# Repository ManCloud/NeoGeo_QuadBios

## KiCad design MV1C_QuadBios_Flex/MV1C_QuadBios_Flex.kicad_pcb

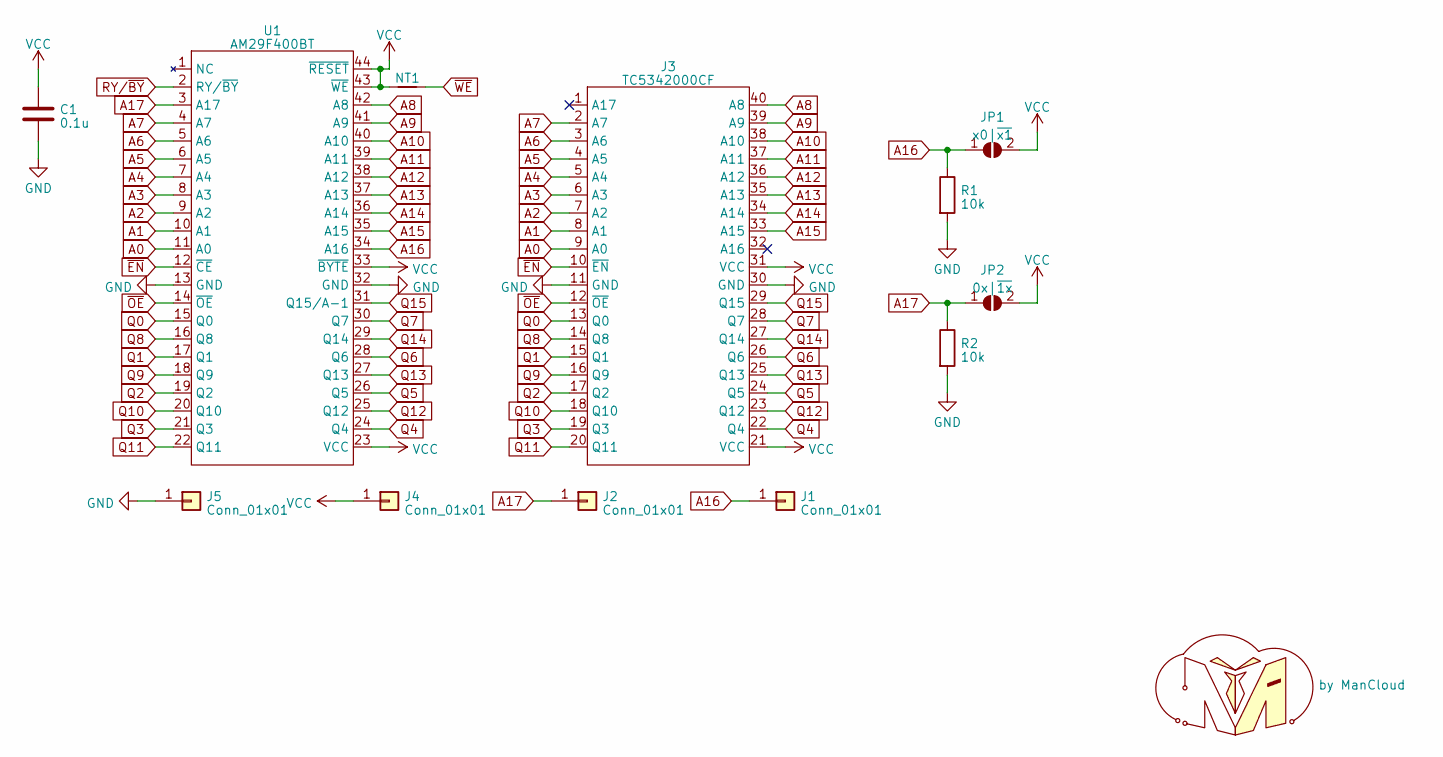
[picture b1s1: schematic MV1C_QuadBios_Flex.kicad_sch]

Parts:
C1: 0.1u; C_0603_1608Metric_Pad1.08x0.95mm_HandSolder
J1, J2, J4, J5: Conn_01x01; TestPoint_Keystone_5015_Micro-Minature
J3: TC5342000CF; TSOP-40_26.0x10.0mm_P1.27mm_JIG
JP1: x0|~{x1}; SolderJumper-2_P1.3mm_Open_TrianglePad1.0x1.5mm
JP2: 0x|~{1x}; SolderJumper-2_P1.3mm_Open_TrianglePad1.0x1.5mm
NT1: NetTie_2
R1, R2: 10k; R_0805_2012Metric_Pad1.20x1.40mm_HandSolder
U1: AM29F400BT; SO-44_P1.27
U2: by ManCloud; ManCloud_v2b_22mm

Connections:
A0: J3.9 (A0), U1.11 (A0)
A1: J3.8 (A1), U1.10 (A1)
A2: J3.7 (A2), U1.9 (A2)
A3: J3.6 (A3), U1.8 (A3)
A4: J3.5 (A4), U1.7 (A4)
A5: J3.4 (A5), U1.6 (A5)
A6: J3.3 (A6), U1.5 (A6)
A7: J3.2 (A7), U1.4 (A7)
A8: J3.40 (A8), U1.42 (A8)
A9: J3.39 (A9), U1.41 (A9)
A10: J3.38 (A10), U1.40 (A10)
A11: J3.37 (A11), U1.39 (A11)
A12: J3.36 (A12), U1.38 (A12)
A13: J3.35 (A13), U1.37 (A13)
A14: J3.34 (A14), U1.36 (A14)
A15: J3.33 (A15), U1.35 (A15)
A16: J1.1, JP1.1 (A), R1.1, U1.34 (A16)
A17: J2.1, JP2.1 (A), R2.1, U1.3 (A17)
GND: C1.2, J3.11 (GND), J3.30 (GND), J5.1, R1.2, R2.2, U1.13 (GND), U1.32 (GND)
Q0: J3.13 (Q0), U1.15 (Q0)
Q1: J3.15 (Q1), U1.17 (Q1)
Q2: J3.17 (Q2), U1.19 (Q2)
Q3: J3.19 (Q3), U1.21 (Q3)
Q4: J3.22 (Q4), U1.24 (Q4)
Q5: J3.24 (Q5), U1.26 (Q5)
Q6: J3.26 (Q6), U1.28 (Q6)
Q7: J3.28 (Q7), U1.30 (Q7)
Q8: J3.14 (Q8), U1.16 (Q8)
Q9: J3.16 (Q9), U1.18 (Q9)
Q10: J3.18 (Q10), U1.20 (Q10)
Q11: J3.20 (Q11), U1.22 (Q11)
Q12: J3.23 (Q12), U1.25 (Q12)
Q13: J3.25 (Q13), U1.27 (Q13)
Q14: J3.27 (Q14), U1.29 (Q14)
Q15: J3.29 (Q15), U1.31 (Q15/A-1)
RY/~BY: U1.2 (RY/~BY)
VCC: C1.1, J3.21 (VCC), J3.31 (VCC), J4.1, JP1.2 (B), JP2.2 (B), NT1.1, U1.23 (VCC), U1.33 (~BYTE), U1.43 (~WE), U1.44 (~RESET)
~EN: J3.10 (~EN), U1.12 (~CE)
~OE: J3.12 (~OE), U1.14 (~OE)

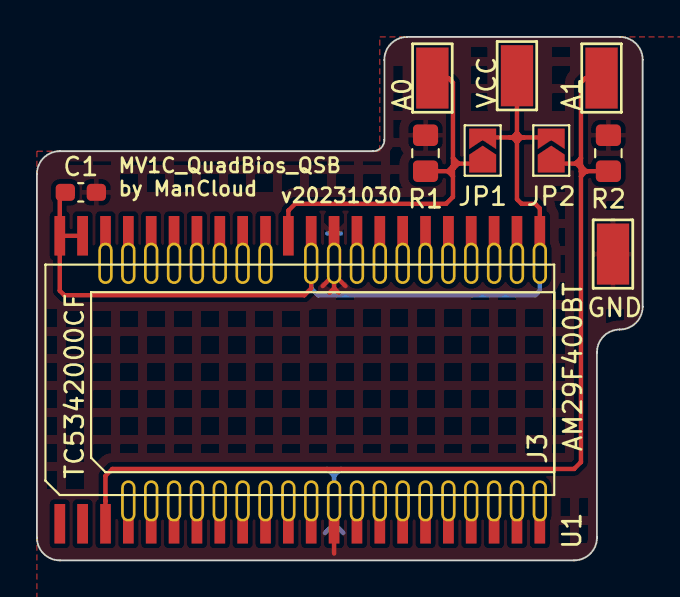
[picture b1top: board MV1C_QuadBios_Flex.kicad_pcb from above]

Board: 2 copper layers, 33.7 x 29.1 mm, 12 parts (1 on the bottom side), 38 nets.

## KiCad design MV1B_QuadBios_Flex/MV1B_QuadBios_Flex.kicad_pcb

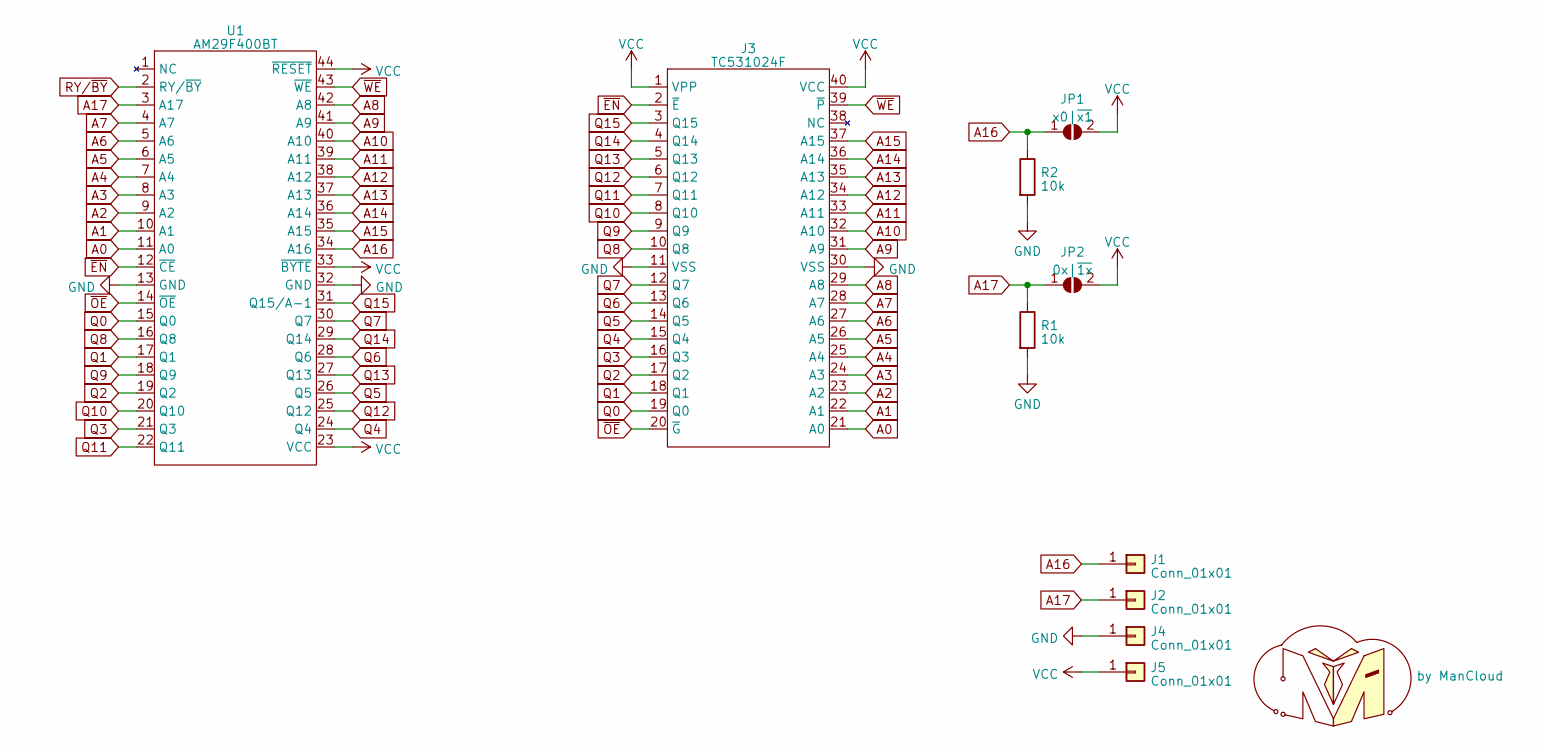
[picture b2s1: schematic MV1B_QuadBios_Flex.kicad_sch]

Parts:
J1, J2, J4, J5: Conn_01x01; TestPoint_Keystone_5015_Micro-Minature
J3: TC531024F; TSOP-40_26.0x10.0mm_P1.27mm_JIG
JP1: x0|~{x1}; SolderJumper-2_P1.3mm_Open_TrianglePad1.0x1.5mm
JP2: 0x|~{1x}; SolderJumper-2_P1.3mm_Open_TrianglePad1.0x1.5mm
R1, R2: 10k; R_0805_2012Metric_Pad1.20x1.40mm_HandSolder
U1: AM29F400BT; SO-44_P1.27
U2: by ManCloud; ManCloud_v2b_22mm

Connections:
A0: J3.21 (A0), U1.11 (A0)
A1: J3.22 (A1), U1.10 (A1)
A2: J3.23 (A2), U1.9 (A2)
A3: J3.24 (A3), U1.8 (A3)
A4: J3.25 (A4), U1.7 (A4)
A5: J3.26 (A5), U1.6 (A5)
A6: J3.27 (A6), U1.5 (A6)
A7: J3.28 (A7), U1.4 (A7)
A8: J3.29 (A8), U1.42 (A8)
A9: J3.31 (A9), U1.41 (A9)
A10: J3.32 (A10), U1.40 (A10)
A11: J3.33 (A11), U1.39 (A11)
A12: J3.34 (A12), U1.38 (A12)
A13: J3.35 (A13), U1.37 (A13)
A14: J3.36 (A14), U1.36 (A14)
A15: J3.37 (A15), U1.35 (A15)
A16: J1.1, JP1.1 (A), R2.1, U1.34 (A16)
A17: J2.1, JP2.1 (A), R1.1, U1.3 (A17)
GND: J3.11 (VSS), J3.30 (VSS), J4.1, R1.2, R2.2, U1.13 (GND), U1.32 (GND)
Q0: J3.19 (Q0), U1.15 (Q0)
Q1: J3.18 (Q1), U1.17 (Q1)
Q2: J3.17 (Q2), U1.19 (Q2)
Q3: J3.16 (Q3), U1.21 (Q3)
Q4: J3.15 (Q4), U1.24 (Q4)
Q5: J3.14 (Q5), U1.26 (Q5)
Q6: J3.13 (Q6), U1.28 (Q6)
Q7: J3.12 (Q7), U1.30 (Q7)
Q8: J3.10 (Q8), U1.16 (Q8)
Q9: J3.9 (Q9), U1.18 (Q9)
Q10: J3.8 (Q10), U1.20 (Q10)
Q11: J3.7 (Q11), U1.22 (Q11)
Q12: J3.6 (Q12), U1.25 (Q12)
Q13: J3.5 (Q13), U1.27 (Q13)
Q14: J3.4 (Q14), U1.29 (Q14)
Q15: J3.3 (Q15), U1.31 (Q15/A-1)
RY/~BY: U1.2 (RY/~BY)
VCC: J3.1 (VPP), J3.40 (VCC), J5.1, JP1.2 (B), JP2.2 (B), U1.23 (VCC), U1.33 (~BYTE), U1.44 (~RESET)
~EN: J3.2 (~E), U1.12 (~CE)
~OE: J3.20 (~G), U1.14 (~OE)
~WE: J3.39 (~P), U1.43 (~WE)

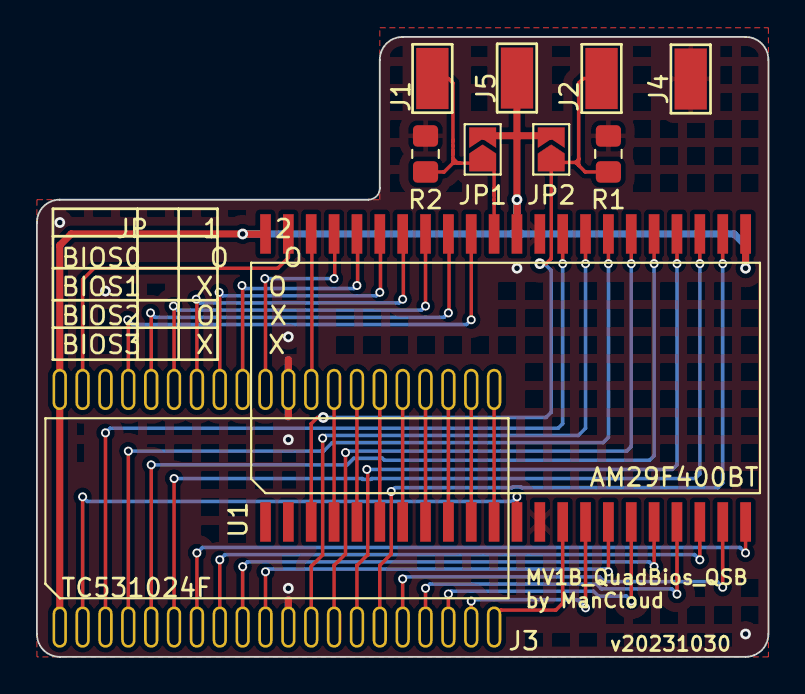
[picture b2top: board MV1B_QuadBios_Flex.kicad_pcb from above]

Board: 2 copper layers, 40.6 x 34.4 mm, 11 parts (1 on the bottom side), 39 nets.
